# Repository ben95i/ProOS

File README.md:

# ProOS

ProOS is a self-hosted home automation and home server platform by Ben Provenzano III. It holds the configuration, firmware and code for every machine on the home network, from a Proxmox server down to a Pico W lamp controller, and one web app, **Automate**, controls all of it from a phone or browser.

The system has three layers. At the centre is one Proxmox server, which routes the network and runs storage, media, backups and the Automate web app in containers and VMs. Around the apartment, Raspberry Pis each take one role, such as a LED display, an audio receiver, a camera or a serial bridge. Below them, Pico W and Arduino microcontrollers switch the lamps, amps, outlets and bed. A button press in Automate goes to its API on the server, which calls the Pi or microcontroller that owns the device, so the browser never talks to the hardware directly. Every machine is defined entirely by its folder in this repo and is rebuilt over the network from a stock OS install, so any host can be replaced from scratch.

### Features

- **Automate web app.** One page that drives the apartment room by room: lamps and dimmers, ceiling lights, TVs, PCs (wake-on-LAN, sleep, power relays), the stereo amps' power, inputs, volume and subwoofers, the motorised bed and its LED strip, and the bathroom's motion-sensing light. Also live room status, scenes (room, lights, all on / off), temperature and humidity, weather, network host status, bookmarks, encrypted shared lists, photo and video upload, and a live doorway camera.
- **LED pixels.** Pis drive LED walls, grids and strips through Fadecandy or WS2812 directly, with C++ effects (text scroll, spectrum, maze, noise, orbits and more), video playback on the pixels, shuffle, and per-host brightness, kept in sync from one control.
- **Raspberry Pi modules.** A shared Pi base plus one small module per Pi: AirPlay and Bluetooth audio receivers, LED hosts, IR and motion-recording cameras with cloud upload, and the bedroom hub's serial bridge. Each Pi runs a read-only root filesystem so it survives losing power, recovers its own Wi-Fi, falls back to a setup hotspot, and compiles its C/C++ programs on install.
- **Microcontroller firmware.** Pico W lamp and light controllers and an HVAC thermostat (SmartThermo) with their own HTTP API, and Arduino/AVR boards for the bedroom hub, bed motor, switched outlets, the integrated amp and an IR remote hub.
- **Home server.** A Proxmox host running the services as containers and VMs: the router, SMB file shares (including one for vintage clients), an AFP server for classic Macs, Jellyfin with automatic MP3 mirroring, a UniFi controller, and a sandboxed desktop with a VPN kill switch. ZFS mirrored storage with automatic snapshots, rsync backups to encrypted external pools, encrypted on-demand storage regions, UPS monitoring, and backups of every VM and container, all triggered from the website.
- **One-command deployment.** `login.sh` deploys any host from this repo over SSH, with one passphrase prompt per terminal session for all keys.

The Automate website (`shared/html`, `shared/nodeapi`) has its own full reference, [`shared/CLAUDE.md`](shared/CLAUDE.md), imported at the end of this file.

## The system at a glance

One Proxmox server (`pve`) runs the network's services as LXC containers and KVM VMs. Raspberry Pis around the apartment each run one "module" (LEDs, cameras, audio), and small microcontrollers (Pico W, Arduino) drive lamps, amps and the bed. The Automate website, served from the `automate` container, is the remote control for all of it.

```
                    browser / phone
                          │  https://automate.home
                          ▼
  ┌─────────────────────────── pve (Proxmox, 192.168.1.8) ──────────────────────────┐
  │  automate LXC 106 ── lighttpd → node API ──┬─ HTTP → Pis (port 80 /api)          │
  │      /var/www/html/ram  ═══ bind ═══╗      ├─ HTTP → Pico W lamps (port 4000)    │
  │                                     ║      └─ LED hosts (ledhosts.txt)           │
  │  host tmpfs /mnt/ramdisk ◄══════════╝                                            │
  │      ▲ file-monitor.sh → apicmds.sh (backups, regions, start/stop VMs)           │
  │  files LXC 101 (SMB) · mgmt LXC 102 · legacy LXC 104 · media LXC 108             │
  │  router VM 100 · appletalk VM 103 · xana VM 105 · unifi VM 107                   │
  │  ZFS: rpool (boot) · tank/datastore (data, mirrored) · scratch SSD · ext. backups │
  └──────────────────────────────────────────────────────────────────────────────────┘
       Pis: brpi · ledwall · ledgrid · ledstrip · doorway · homepi · btpi · lrpi
       Microcontrollers: BathroomLight, LivingRoomLamp, SmartThermo (Pico W) · Bedroom hub, amp, IR hub (AVR)
```

## Folder map

Every top-level folder is one of four kinds. `login.sh` tells them apart by the marker file in the folder: `lxc.conf`, `qemu.conf` or `pc.conf` means a server ("nonpi"), anything else is a Pi module.

| Kind | Folders | Layout | Deployed by |
| --- | --- | --- | --- |
| Pi base | `rpi/` | Programs, `config/` (installer, systemd units, system configs), `effects/` (LED programs) | Copied to every Pi first, to `/opt/rpi` |
| Pi module | `brpi` `btpi` `doorway` `homepi` `ledgrid` `ledstrip` `ledwall` `lrpi` | `boot.sh`, `config/` (`installer.sh`, `brand.txt`, `config.txt`, other configs), extra programs or firmware | Overlaid onto `/opt/rpi` after the base, with `config/` sent to `/opt/rpi/config/module/` |
| Server (LXC / VM / PC) | `automate` `files` `legacy` `media` `mgmt` (LXC); `appletalk` `xana` (VM); `pve` (the Proxmox host); `brpc` (a physical PC) | `config/installer.sh` plus the files it installs; `lxc.conf` / `qemu.conf` / `pc.conf` marker | Tarred to `/tmp/config` and `installer.sh` run |
| Not deployed | `shared/` (Automate site, deployed with `automate` and every Pi), `wkst/` (this workstation, `install.sh` run by hand) | | |

`login.sh` refuses `rpi`, `wkst`, `shared`, `sources`, `login`, `logon` and `.ssh` as host names.

## Network and hosts

DNS domain `home`, LAN 192.168.1.0/24, gateway and DNS the router at 192.168.1.1. Addresses known from the code:

| Host | Kind | Address | What it is |
| --- | --- | --- | --- |
| `router` | VM 100 | 192.168.1.1 | The router, with two NICs passed through over PCIe (`hostpci0/1`); login is `admin@router`, not root. Configs in `pve/network/` (pfSense, EdgeRouter, UniFi backups) |
| `files` | LXC 101 | .4 | Samba file server (SMB2+): shares Data, Media, Scratch, Cameras, Games, MP3s, Regions, External |
| `mgmt` | LXC 102 | .7 | Management box: holds the SSH keys (`mgmt/keys/`, git-ignored) and runs `login.sh`; mounts the Projects share read-only at `/mnt/Projects` |
| `pve` | Proxmox host | .8 | Hypervisor; 4 NICs bonded 802.3ad into `vmbr0` |
| `appletalk` | VM 103 | | Netatalk 4 AFP server (built from `netatalk-4.4.3.tar.xz`) for vintage Macs |
| `legacy` | LXC 104 | .19 | Samba with `LANMAN1` minimum protocol, for old clients; started on demand from the website |
| `xana` | VM 105 | | Debian desktop over TigerVNC: Firefox in Firejail, Transmission behind a PIA WireGuard tunnel with kill switch and watchdog, retro themes |
| `automate` | LXC 106 | .16 | The Automate website and node API |
| `unifi` | VM 107 | | UniFi network controller |
| `media` | LXC 108 | .11 | Jellyfin, plus `mp3sync` (C++, `mp3sync.cpp`): watches the music library with inotify and mirrors it as MP3s into the MP3s share |
| `brpc` | PC | .17 | Bedroom Lenovo ThinkCentre: its own lighttpd + node API (`server-min.js`) and `webapi.sh` so Automate can sleep it; woken by wake-on-LAN |
| `brpi` | Pi | .15 | Bedroom Pi (wired, Wi-Fi off): AirPlay, serial bridge to the bedroom hub and the amp, relax sounds |
| `ledwall` | Pi | .12 (`lrxmit` in the API) | LEDwall: the 93-pixel LED ring (Fadecandy) and the living room's command host. Its `custom.js` serves `extcom` (living room stereo codes over serial on `/dev/ttyAMA0`), the white LED, the front button and the desktop PC power relay (`pc_power`) |
| `ledgrid` | Pi Zero | | WS2812 grid driven directly (`opcserver`) |
| `ledstrip` | Pi | | 3×60 strips (Fadecandy) |
| `doorway` | Pi | | IMX462 IR camera: `rtspcam` (RTSP on :8554/cam), `minimotion` recorder, `ldrdetect` day/night, rclone to Google Drive, Cameras share |
| `homepi` | Pi | | Family-home camera hub: `motion` with two cameras, uploads via rclone |
| `btpi` · `lrpi` | Pi | | Audio receivers: AirPlay (shairport-sync) and Bluetooth (BlueALSA) into a stereo; `btpi` adds Bluetooth to a vintage stereo, `lrpi` (formerly `stereo`) is the living room's, branded "Living Room" |
| `desk` | PC | .14 | Living room desktop, pinged by `wkststate` |
| `lrmlamp1` · `bthrlight1` | Pico W | .18 · .21 | Living room lamp, bathroom light (firmware in `automate/devices/`) |
| `lrthermo1` | Pico W | .3 | SmartThermo, the living room's HVAC thermostat (firmware in `automate/devices/SmartThermo/`) |
| `wkst` | Workstation | | This machine: mounts the `files` shares under `/mnt/*` with autofs (`auto.files`), detached while `files` is down by `share-watchdog.sh` (so this repo, `/mnt/Data/Projects/ProOS`, is the Data share) |

The Automate status menu (`shared/html/menus/statsmenu.txt`) and the LED host list (`menus/ledhosts.txt`) are the living lists of hosts the website talks to.

## Deployment: `login.sh`

`login.sh` runs on `mgmt`, where the repo is at `/mnt/Projects/ProOS` (its `ROOTDIR`), and needs `/opt/deploy` as a scratch folder. A host's key (`mgmt/keys/<host>.rsa` for servers, `rpi.rsa` for all Pis) has a passphrase when the host's folder holds an empty `ssh.pwd` marker file (`<host>/ssh.pwd`; for the Pi key, `rpi/ssh.pwd` or any Pi module's); all marked keys share one passphrase. Marked keys go through one `ssh-agent` per terminal session (keyed by the calling shell's PID, socket under `$XDG_RUNTIME_DIR/ssh-agents/`, or `/dev/shm/proos-<uid>/` without it): the first marked login in a terminal adds every marked key in one `ssh-add` call, so a single `Enter passphrase:` prompt unlocks them all (the script is its own `SSH_ASKPASS` prompter, run through bash by a two-line `askpass` wrapper it writes into the session folder, so no key path is shown; Enter skips a key for the rest of the session), and later runs reuse the agent. Unmarked keys are used straight from the file. Each connection uses `-o IdentitiesOnly=yes -i` with the host's key (its public key taken from the agent when unlocked), so ssh never offers the other loaded keys. The agent is removed by `login clearkeys`, by the `EXIT` trap in `mgmt/config/profile_ben`, when its shell is gone, or after 8 h; the passphrase itself is never stored. It checks port 22 with `nc`, then:

| Command | Does |
| --- | --- |
| `login <host>` | SSH shell as root (`admin` for `router`) |
| `login <host> sync` | Deploy: server → `DEPLOY_SERVER`, Pi → `DEPLOY_PI` |
| `login <pi> reset` | Deploy a Pi after deleting `/etc/rpi-conf.done`, so the installer's first-run phase runs again |
| `login <module> init <host>` | Deploy module `<module>` onto the Pi currently reachable as `<host>` (renames it to `<module>`) |
| `login <host> update` | Updates the host's packages: `apt-get update; apt-get upgrade` on a server, `rpi update` on a Pi. Given a host list (`login pve,files,automate update`), every host updates at once in its own tile |
| `login <host> reboot` | Reboots a server or a Pi after a 3 s Ctrl+C countdown (a Pi keeps its read-only or read-write mode); `login files,legacy reboot` reboots each in its own tile |
| `login <pi> <cmd>` | Runs `rpi <cmd>` on the Pi (see `rpi/rpi.sh`) |
| `login <host1>,<host2>,… [<cmd>]` | Opens one tmux tile per host (a new window when already inside tmux), each running `login <host> [<cmd>]` with the same `<cmd>` (not `init`). The keys are unlocked once before the tiles open and the tiles share that terminal's agent (`PROOS_AGENT_DIR`); each tile waits for a key before it closes. `mgmt` installs `/etc/tmux.conf` with `mouse on`, so a click selects a tile |
| `login clearkeys` | Forget this terminal's unlocked keys (stops its agent) |
| `login cmds` · `login rmtmp` | Command cheat sheet · delete deploy temp files and stop every session agent |

**A new Pi.** Start from stock Raspberry Pi OS with root SSH login and password authentication enabled, then run `login <module> init <host>`: the first connection falls back to the root password, and the installer replaces root's `authorized_keys` with `rpi/config/authorized_keys` (the public half of `mgmt/keys/rpi.rsa`, git-ignored) and installs an `sshd_config` that allows root by key only (`PermitRootLogin without-password`, `PasswordAuthentication no`).

After a deploy a menu offers re-deploy, update packages, reboot (a Pi reboots into read-only mode with `rpi ro`) or a shell.

**Server deploy.** Copies `<host>/config` to a temp folder (for `automate`, also `shared/html` and `shared/nodeapi` into it), tars it, `scp`s it to `/tmp`, untars to `/tmp/config` and runs `/tmp/config/installer.sh` as root. Every server installer follows the same shape: apt packages, users (`tank` uid 1000 and group `shared` gid 1000, which the LXC idmaps pass through unshifted), sshd config and `authorized_keys`, `profile`, `sysctl.conf`, `rc.local` + `rc-local.service` as the boot hook, service files, then deletes `/tmp/config`.

**Site icons.** The Automate site's Font Awesome sheet and fonts (`styles/icons.min.css`, `fonts/fa-*.woff2`) are not in the repo; they live only in the cache `/tmp/proos-fontcache` on `mgmt` (the repo is read-only there). Before every deploy of the site (`automate` and every Pi), `login.sh` checks the cache against the site with `shared/fontawesome/build-icons.py --check`, builds into it with `build-icons.py --out` when a page names an icon it lacks (or after a reboot cleared `/tmp`), and copies the cached files into the deploy's copy of the site (a work folder under `/opt/deploy` for a Pi), each step printed as an `Icons:` line. The cache stays after a deploy, so later deploys reuse it, and a lock file in it makes parallel deploys (tmux tiles) take turns. A failed build sends the cache's older build with a warning (icons added since show blank); with no build at all, or a cache that cannot be written, the site goes with every icon blank, also with a warning. The build needs `python3-fonttools` and `python3-brotli`, which `mgmt/config/installer.sh` installs.

**Pi deploy.** If the root filesystem is an overlay it first runs `rpi rw` and waits for the reboot. Then it rsyncs, in order: `rpi/` → `/opt/rpi`, a copy of `shared/html/` with the icons from the cache → `/opt/rpi/config/html/`, `shared/nodeapi/` → `/opt/nodeapi/`, `<module>/` → `/opt/rpi/` (excluding `config`, `photos` and `sources`), and `<module>/config/` → `/opt/rpi/config/module/` (replacing what an earlier deploy left there), writes the module name to `/opt/rpi/config/hostname` and runs `/opt/rpi/config/installer.sh`.

Because the module is copied over the base, **a module's files replace the base's files of the same name**: `<module>/boot.sh` replaces `rpi/boot.sh`. The one exception is the module's `config/`, which lands beside the base's as `/opt/rpi/config/module/`, so its `installer.sh` and `config.txt` do not replace the base's.

## Raspberry Pi platform (`rpi/`)

Requires Raspberry Pi OS on Debian **trixie**; the installer refuses anything else.

### Installer (`rpi/config/installer.sh`)

1. **First run only** (no `/etc/rpi-conf.done`): locale, time zone, `pi` user, a long apt package list (build tools, GStreamer, ffmpeg, Bluetooth, node, lighttpd, motion; no X11 desktop), purges cron, logrotate, swap, PulseAudio/PipeWire, cups and others, deletes old `rpi-*` units.
2. **Every run**: read-only boot partition, `config.txt`, sshd and key, `sysctl`, NetworkManager, journald (to RAM), systemd units from `config/systemd/` into `/etc/systemd/system/`, `/etc/netmode.sh` and `/etc/preinit.sh`.
3. **Node API**: moves `rpi/controller.js`, `rpi/ledparser.js` and `rpi/custom.js` over the shared ones in `/opt/nodeapi` (`npm install` only when `package.json` changed, tracked in `.deps.hash`).
4. **Website**: rsyncs the staged html into `/var/www/html` (keeping `ram/`), replaces the title `>Automate<` with the module's `brand.txt` name (this is how `main.js` picks the Pi or LED Pi page model), minifies, and gives `www-data` sudo on `servercmds.sh` and `relaxrun.sh` only.
5. Bluetooth, ALSA, Samba USB share, udev USB automount, motion defaults, hostname and `/etc/hosts`.
6. **`config/cleanup.sh`**, once per Pi (skipped while `/etc/rpi-cleanup.done` exists; delete it and deploy to run it again), so the system fits an 8 GB card: swaps `libopencv-dev` for `libopencv-core-dev` + `libopencv-videoio-dev`; purges the X11 desktop, the `arduino` apt package and its AVR toolchain, USB Wi-Fi dongle firmware, the `v6` kernels, every kernel but the running and newest, and all kernel headers; deletes `arduino-cli` and `~/.arduino15` unless the module's `config/installer.sh` installs it (only `brpi` does); installs `config/dpkg-nodoc.conf` as `/etc/dpkg/dpkg.cfg.d/01-nodoc` and deletes docs, man pages and non-English translations; clears the apt lists and npm cache.
7. **`config/compile.sh`**: builds the C/C++ programs (below).
8. First run: enables `ssh avahi-daemon proinit NetworkManager timesyncd`, disables the rest (lighttpd, bluetooth, smbd, hostapd …), touches `/etc/rpi-conf.done`.
9. Runs `/opt/rpi/config/module/installer.sh` (the module's own installer, from `<module>/config/installer.sh`), then **deletes `/opt/rpi/config/module`**; restarts lighttpd and nodeapi; links `/usr/bin/rpi` → `rpi.sh`; deletes `/opt/rpi/config`.

### Boot sequence

`proinit.service` (after `network-online.target`) runs `/etc/netmode.sh boot`, then `/opt/rpi/boot.sh` — the module's own boot script. Module boot scripts start only the services that module needs, passing settings through `systemctl set-environment` (e.g. `rpi_ledtype`, `rpi_ledmaxbright`, `rpi_gpipin_1`, `rpi_imx*`), which the `rpi-*.service` units read. Nothing module-specific is enabled at boot; services are started by `boot.sh`.

### Read-only root

Pis run with an OverlayFS root, so writes go to RAM and the Pi can be unplugged safely (the SD cards used to corrupt when a Pi lost power). `rpi rw` / `rpi ro` reboot into read-write / read-only (via `raspi-config nonint disable_overlayfs`/`enable_overlayfs`); the boot partition is remounted rw only for the moment it is written. Anything that must survive a reboot on a Pi has to be written in rw mode or to the boot partition / a USB drive.

### Networking (`rpi/config/netmode.sh`)

`boot`, `client`, `apd`, `delwifi`, `watchdog`. Wi-Fi credentials live on the boot partition (`/boot/firmware/wpa.conf`, `NAME|$|PASSWORD`, written by the website's Wi-Fi setup through `servercmds.sh confwpa`). Flags on the boot partition: `disable.wifi`, `apd.enable` (start as hotspot `RPiHotspot`). With no known network at boot the Pi falls back to hotspot mode with a captive DNS (`captive.conf`). `rpi-netwatchdog.service` (`netmode.sh watchdog`) recovers a hung Wi-Fi chip in stages without writing to disk; tunables are at the top of the script.

### `rpi` command (`rpi/rpi.sh`)

`ro`, `rw`, `update`, `expand`, `net`, `wifiscan`, `wifistats`, `togglenet`, `client`, `apd`, `apdonboot`, `enablewifi`/`disablewifi`, `delwifi`, `resetbt`, `restart-alsa`, `temp`, `jl`/`jh` (journal), `running`/`active`/`timers`/`loadtimes`. The website's Pi options call these through `servercmds.sh`, which logs to `/var/www/html/ram/sysout.txt`.

### Pi-side node API

The Pis run the same `shared/nodeapi/server.js`, but `rpi/controller.js` replaces the server's command dispatch: `server <cmd>` → `sudo servercmds.sh <cmd>`, `confwpa` → Wi-Fi setup, everything else → `exeCustom()` in `custom.js`. The base `rpi/custom.js` is a stub; a module with real commands ships `config/custom.js`, which its `config/installer.sh` copies over it:

- `brpi/config/custom.js`: serial via `ztermcom` (one FIFO queue, at most 8 waiting) to the amp on `/dev/ttyUSB0` and the bedroom hub on `/dev/ttyAMA0` (`hwcom`, `usbcom`), amp power/inputs/volume, `bed_leds_hex_set`, relax sounds (`relaxmenu.txt`, `relaxrun.sh` → `rpi-relaxloop.service`), activity LED flash.
- `ledwall/config/custom.js`: `extcom` (serial), `front_btn` (LED shuffle), white LED, `pc_power`.

`rpi/ledparser.js` replaces the server's LED fan-out with the local effect runner: it spawns one effect binary from `/opt/rpi/effects`, plays videos through `mp4toleds`, and sets brightness through the proxy. Shuffle picks from `menus/ledshuffle.txt`. Each command also records what the pixels show, which `fc_status` (`/api?action=leds&arg=fc_status`) answers as JSON with the brightness: `{ effect, state, color, brightness }`, state `off` (stopped, or black), `active`, `paused` (also an effect that ended on its own) or `color` (RRGGBB); the server's Pixels window reads it.

### Local services and ports

| Program (source) | Unit | Port / interface | Role |
| --- | --- | --- | --- |
| `gposerver` (`gposerver.cpp`) | `rpi-gposerver` | HTTP 127.0.0.1:8770 `/gpio?pin=&state=HIGH\|LOW\|TOGGLE` | GPIO outputs for the node API |
| `pinmon` | `rpi-pinmon-1` | GPIO input | On a falling edge runs `/opt/rpi/<cmd>.sh` (ledwall: `front_btn.sh`, which calls the local API) |
| `ldrdetect` | `rpi-ldrdetect` | GPIO | Light sensor day/night for the camera |
| `opcserver` (`effects/`) | `rpi-opcserver` | OPC :7890, HTTP :7892 | Drives WS2812 directly (ws281x DMA library); args `<WxHgrid> <power limit> <rotation>` |
| `fcserver` (prebuilt) + `fcproxy` | `rpi-fcserver`, `rpi-fcproxy` | effects → :7890 proxy → :7891 fcserver; HTTP :7892 brightness | Fadecandy hosts; layouts in `effects/fc.<ledtype>.json` |
| `mp4toleds` | `rpi-mp4toleds` | OPC client, HTTP :7860 `/api?video=` | Plays `effects/videos/*.mp4` on the pixels |
| Effects: `textscroll maze oscope spectro noise orbits miami stripes chase writecolor` | spawned by `ledparser.js` | OPC client → :7890 | One running at a time; share `ledlayout.cpp` and `opcclient.cpp` |
| `rtspcam` | `rpi-rtspcam` | RTSP :8554/cam | IMX462 hardware H.264 (doorway; notes in `rtspcam.md`) |
| `minimotion` | `rpi-minimotion` | | Motion recorder: reads the RTSP stream, records in `/mnt/ramdisk`, copies clips out (`doorway/minimotion.conf`) |
| `ztermcom` (`ztermcom.c`) | CLI | serial | Framed serial request/response to Arduino hubs |
| node API · lighttpd | `nodeapi`, `lighttpd` | :3000 · :80 | Same as the Automate server |

`ledtype.txt` (written by a LED module's `config/installer.sh`) names the layout: `93ringinv` (ledwall), `3x60strips` (ledstrip), `16x16grid` (ledgrid).

### Compiling (`rpi/config/compile.sh`)

C/C++ sources are compiled on the Pi at install time. `build()` compiles only when the source's sha256 differs from its archived copy in `/opt/source-backup`, the binary is missing, or a shared dependency changed (`opcutils.*` / `httpapiserver.*` for the servers, `ledlayout.*` / `opcclient.*` for the effects); the source is then **moved** into `/opt/source-backup`. A new program needs a `build`/`effect`/`tool` line here. The ws281x library is built once into `/usr/local`.

## Microcontroller firmware

| Folder | Board | Talks to | Role |
| --- | --- | --- | --- |
| `automate/devices/BathroomLight/` | Pico W | HTTP :4000 | Bathroom light + C4002 mmWave sensor; API reference `.md` alongside |
| `automate/devices/LivingRoomLamp/` | Pico W | HTTP :4000 | Living room lamp (switched lamp + dimmable LED, rotary encoder); derived from BathroomLight |
| `automate/devices/SmartThermo/` | Pico W | HTTP :4000 | HVAC thermostat (furnace + central AC): W1 / Y1 / G relays, DHT22, ST7735R TFT display, every interlock and lockout from the HVAC control reference, watchdog; API reference `.md` alongside; derived from BathroomLight |
| `automate/devices/InfraredRemoteHub/` | Arduino | serial | Sends IR codes to the stereo's preamp, DAC and sub amp |
| `brpi/BedroomHub/` | AVR | brpi `/dev/ttyAMA0` | Bedroom hub #1: relays, temperature/humidity (DHT), two external serial ports |
| `brpi/BedroomHubExt/` | ATmega328P | hub serial #2 | WS2812 bed strip, switched outlets, bed motor (EAGLE board files alongside) |
| `brpi/BedroomPowerExt/` | AVR | serial | 2×120 VAC + 12 VDC switched controller |
| `brpi/IntegratedAmp/` | Arduino Uno | brpi `/dev/ttyUSB0` | Integrated amp controller; flashed from the Pi with `brpi/update-amp.sh` (`update-bedhub.sh` for the hub) via `arduino-cli` |

Pico firmware is built with the arduino-pico core (`build/rp2040.rp2040.rpipicow/`, git-ignored); Wi-Fi credentials are in `creds.h` (git-ignored). Pico commands use the `http://<host>:4000/api?<cmd>,,<value>~` form, errors as text under HTTP 200.

## Proxmox host (`pve/`)

`pve/config/installer.sh` sets up the host: no-subscription apt source, NIC name pinning (`50-pve-nic*.link`) and the bonded `interfaces`, IOMMU / PCIe passthrough (`grub`, `blacklist.conf`), swap moved to the scratch SSD, `fstab`, postfix mail relay (`sasl_passwd`, git-ignored), apcupsd (APC SC620 UPS), smartd, lm-sensors, ZFS auto-snapshots on `tank/datastore` (hourly/daily/weekly/monthly cron, no 15-minute), scrub/trim cron, `sys-check` and `kernelclean` tools, and the services below. `pve/qemu.conf` is only a placeholder so `login.sh` treats `pve` as a server. `pve/README.txt` holds the ZFS runbooks (new mirror, encrypted backup drive, replacing a data or boot drive) and `pve/zfsman` is a ZFS helper.

Storage: `rpool` (boot, ZFS), `tank` mirrored with `tank/datastore` at `/mnt/datastore` (`data`, `media`, `.regions`), a scratch SSD at `/mnt/pve/scratch` (camera footage, downloads, MP3s, uploads, swap), encrypted external backup pools listed in `bkpdrives.txt` attached under `/mnt/extbkps`.

### Website → host commands

This is how the Automate Server window controls the host:

1. The host mounts a 128 MB tmpfs at `/mnt/ramdisk` (owner `tank:shared`, setgid), bind-mounted into the automate LXC as `/var/www/html/ram`.
2. The node API's `server <name>` command appends to `ram/sysout.txt` and creates an empty `ram/<name>.txt`.
3. `file-monitor.service` (`pve/config/file-monitor.sh`) watches the ramdisk with inotify, claims each `*.txt` trigger atomically into `spool/`, and runs `/usr/bin/apicmds.sh <name> /mnt/ramdisk` in the background (at most 4 at once), appending output to `sysout.txt`. Data files are on its `IGNORE` list (`sysout.txt`, `*.save.txt`, `*.lock`, `pwd.txt`, `fusearch.txt`, `drives.txt`, `*.tmp`) — a new data file kept in `ram/` must be added there or it will be consumed as a command.
4. The website polls `sysout.txt` into the log window.

`apicmds.sh` commands: `backupstd`, `backupchk` (rsync to external pools, lock `backupsvr.lock`), `last_backup_dates`, `attach_bkps`, `detach_bkps`, region mounts (`mnt_/unmnt_arch_region` gocryptfs Archive, `mnt_/unmnt_ram_region`, `mnt_/unmnt_snap_region`, `unmnt_all`), `pve_listsnaps`, `start/stop` for `legacy` (LXC 104), `xana` (105, plus `restorexana`), `unifi` (107), `atalk` (103), `rebootrouter`, `syslog` (`sys-check`), `pve_vmsbkp`, `clearlog`. A new server command needs a case here and an option in `shared/html/server.js`.

### Persistent state and backups

- **Website state** (`bookmarks.save.txt`, `lists.save.txt`, their lock and password files) lives only in the RAM disk. `hourly.sh` (`hourlyjob.timer`, and `hourlyjob-sd.service` on shutdown) copies them to `/mnt/datastore/data/Documents/` (`Bookmarks.txt`, `Lists.txt`, keeping a `.bak`), and restores them into the RAM disk when they are missing after a reboot.
- **`pve_vmsbkp`** vzdumps every guest, copies the archives into `pve/vmbkps/`, and **overwrites `<host>/lxc.conf`, `appletalk/qemu.conf`, `xana/qemu.conf` and `pve/vmbkps/vzdump-qemu-*.conf` in this repo** from `/etc/pve`. Those files are generated snapshots of the live config: edit the guest in Proxmox, not here.

## Conventions across the repo

Code style rules (naming, comments, shell, JavaScript and CSS) live only in [`CODESTYLE.md`](CODESTYLE.md), imported at the end of this file. This section covers how the repo is organised and worked on.

- A new Pi service is a `rpi-<name>.service` in `rpi/config/systemd/`, not enabled, started from the module's `boot.sh` with settings passed by `systemctl set-environment`.
- A new Pi module is a folder with `boot.sh` and `config/{installer.sh,brand.txt,config.txt}`, the same `config/installer.sh` layout as a server (its installer runs after the base's, from `/opt/rpi/config/module/`); `brand.txt` becomes the page title, AirPlay/Bluetooth/Samba name.
- A new server is a folder with `config/installer.sh` and a marker file; add its key as `mgmt/keys/<name>.rsa`, plus an empty `<name>/ssh.pwd` if the key has the shared passphrase.
- Secrets are git-ignored and must stay out of commits and docs: `mgmt/keys/`, `*.rsa`, `*.pub`, `*.pem`, `*.crt`, `*.key`, `authorized_keys`, `auto.creds`, `creds.h`, `sasl_passwd`, `pia-wg.conf`. Don't print their contents.
- `._*` and `.DS_Store` files are macOS metadata, ignored by git; leave them alone.
- Large binaries in the tree (`pve/vmbkps/*.zst`, `rpi/effects/videos/`, `shared/fontawesome/`, firmware builds, photos) are backups or assets, not sources to read. Photos of the builds are in `btpi/photos`, `ledstrip/photos`, `ledwall/photos` and `pve/photos`, and are not deployed.
- A repo script is run through `bash` (`bash login.sh`, `bash www-minify.sh`), not by its execute bit, which mgmt sees as stored on the server: a file rewritten over the SMB share comes back `0644`, and this workstation's mount shows every file as `0755` whatever it is. A script a program must execute itself (ssh-add's `SSH_ASKPASS`) gets a wrapper written outside the repo; the Pi and server deploys `chmod +x` their installers.
- There is no git or node in this workstation's shell, and no test suite: verify shell changes by reading them, and the website as described in the Automate reference.

Code style: [CODESTYLE.md](CODESTYLE.md)

@CODESTYLE.md

## Automate website reference

Automate reference: [shared/CLAUDE.md](shared/CLAUDE.md)

@shared/CLAUDE.md

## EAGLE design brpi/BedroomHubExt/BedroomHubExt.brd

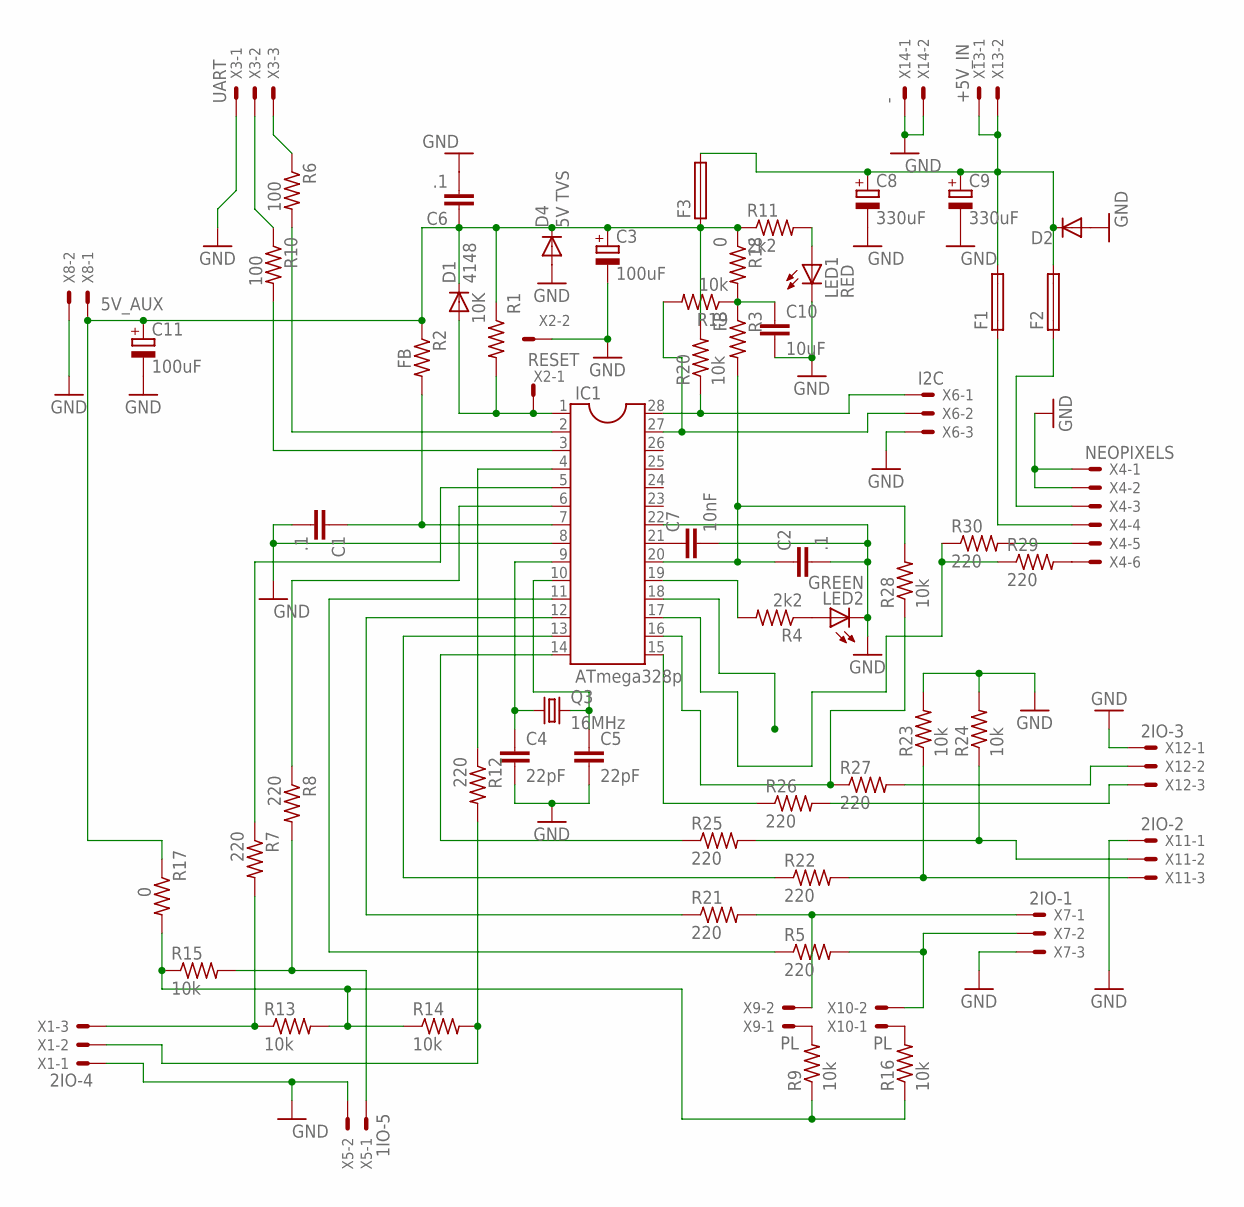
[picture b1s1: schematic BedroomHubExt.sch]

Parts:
C1, C2, C6: .1; C1210K
C3, C11: 100uF; E2,5-7
C4, C5: 22pF; C1210K
C7: 10nF; C050-024X044
C8, C9: 330uF; E5-10,5
C10: 10uF; C1210K
D1: 4148; DO35-7
D2: 1N5624; DO201-15
D4: 5V TVS; DO07
F1, F2, F3: 19560
IC1: ATmega328p; DIL28-3
LED1: RED; LED3MM
LED2: GREEN; LED3MM
Q3: 16MHz; HC49/S
R1: 10K; 0309/10
R2, R3: FB; 0309/10
R4, R11: 2k2; 0309/10
R5, R21, R22, R25: 220; 0207/7
R6, R10: 100; 0309/10
R7, R8, R12, R26, R27, R29, R30: 220; 0309/10
R9, R13, R14, R15, R16, R19, R20, R23, R24: 10k; R1210
R17, R18: 0; 0309/10
R28: 10k; 0309/10
X1: 2IO-4; 22-23-2031
X2: RESET; 22-23-2021
X3: UART; 22-23-2031
X4: NEOPIXELS; 22-23-2061
X5: 1IO-5; 22-23-2021
X6: I2C; 22-23-2031
X7: 2IO-1; 22-23-2031
X8: 5V_AUX; 22-23-2021
X9, X10: PL; 22-23-2021
X11: 2IO-2; 22-23-2031
X12: 2IO-3; 22-23-2031
X13: +5V_IN; 22-23-2021
X14: -; 22-23-2021

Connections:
GND: C1.2, C2.2, C3.-, C4.2, C5.2, C6.2, C7.2, C8.-, C9.-, C10.2, C11.-, D2.A, D4.A, IC1.8, IC1.22, LED1.K (C), LED2.K (C), R23.2, R24.2, X1.1, X2.2, X3.1, X4.1, X4.2, X5.2, X6.3, X7.3, X8.2, X11.1, X12.1, X14.1, X14.2
unnamed: IC1.2, R6.2
unnamed: D1.A, IC1.1, R1.2, X2.1
unnamed: IC1.3, R10.2
unnamed: C2.1, IC1.20, R3.2, R28.2
unnamed: R24.1, R25.2, X11.2
unnamed: R26.2, X12.3
unnamed: LED1.A, R11.2
unnamed: IC1.19, R4.2
unnamed: IC1.15, R26.1
unnamed: IC1.16, R27.1, R28.1
unnamed: IC1.17, R29.1, R30.1
unnamed: C4.1, IC1.9, Q3.1
unnamed: C5.1, IC1.10, Q3.2
unnamed: C7.1, IC1.21
unnamed: LED2.A, R4.1
unnamed: IC1.14, R25.1
unnamed: IC1.13, R22.1
unnamed: IC1.12, R21.1
unnamed: IC1.11, R5.1
unnamed: IC1.6, R8.1
unnamed: IC1.5, R7.1
unnamed: IC1.4, R12.1
unnamed: C3.+, C6.1, C11.+, D1.C, D4.C, F3.1, R1.1, R2.1, R11.1, R17.1, R18.1, R20.2, X8.1
unnamed: R10.1, X3.2
unnamed: R7.2, R13.1, X1.3
unnamed: R8.2, R15.2, X5.1
unnamed: R5.2, X7.2, X10.2
unnamed: R21.2, X7.1, X9.2
unnamed: R12.2, R14.2, X1.2
unnamed: C1.1, IC1.7, R2.2
unnamed: R6.1, X3.3
unnamed: IC1.28, R20.1, X6.1
unnamed: R9.1, R13.2, R14.1, R15.1, R16.1, R17.2
unnamed: IC1.27, R19.2, X6.2
unnamed: C10.1, R3.1, R18.2, R19.1
unnamed: R22.2, R23.1, X11.3
unnamed: R9.2, X9.1
unnamed: R16.2, X10.1
unnamed: R27.2, X12.2
unnamed: R29.2, X4.6
unnamed: R30.2, X4.5
unnamed: F1.1, X4.4
unnamed: F2.1, X4.3
unnamed: C8.+, C9.+, D2.C, F1.2, F2.2, F3.2, X13.1, X13.2

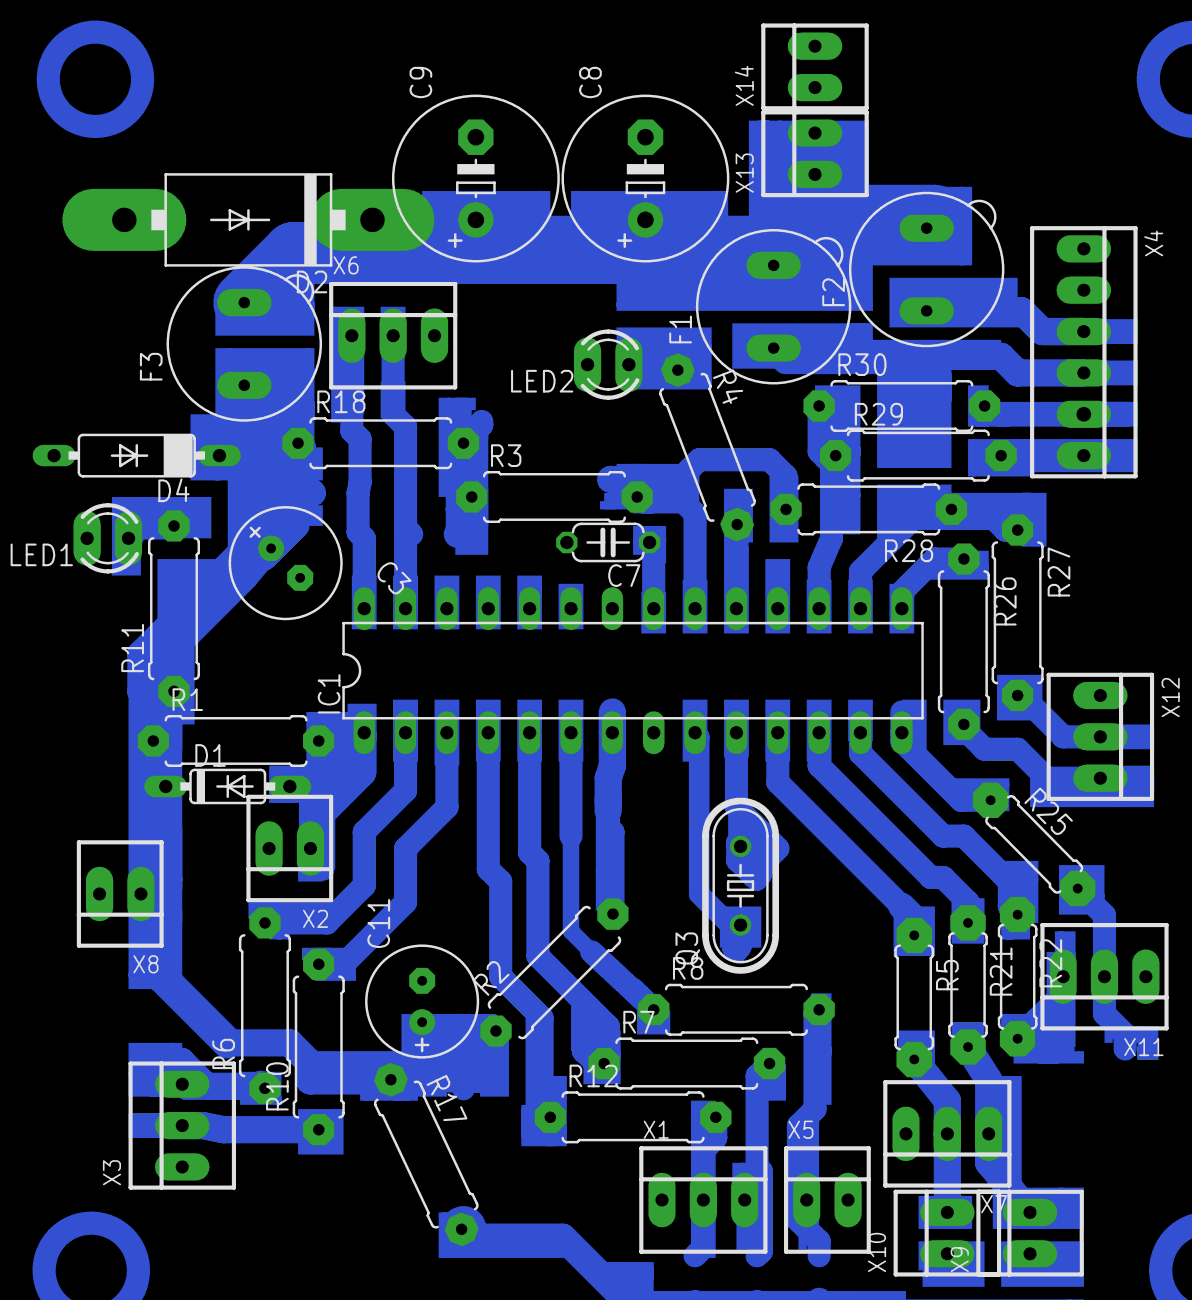
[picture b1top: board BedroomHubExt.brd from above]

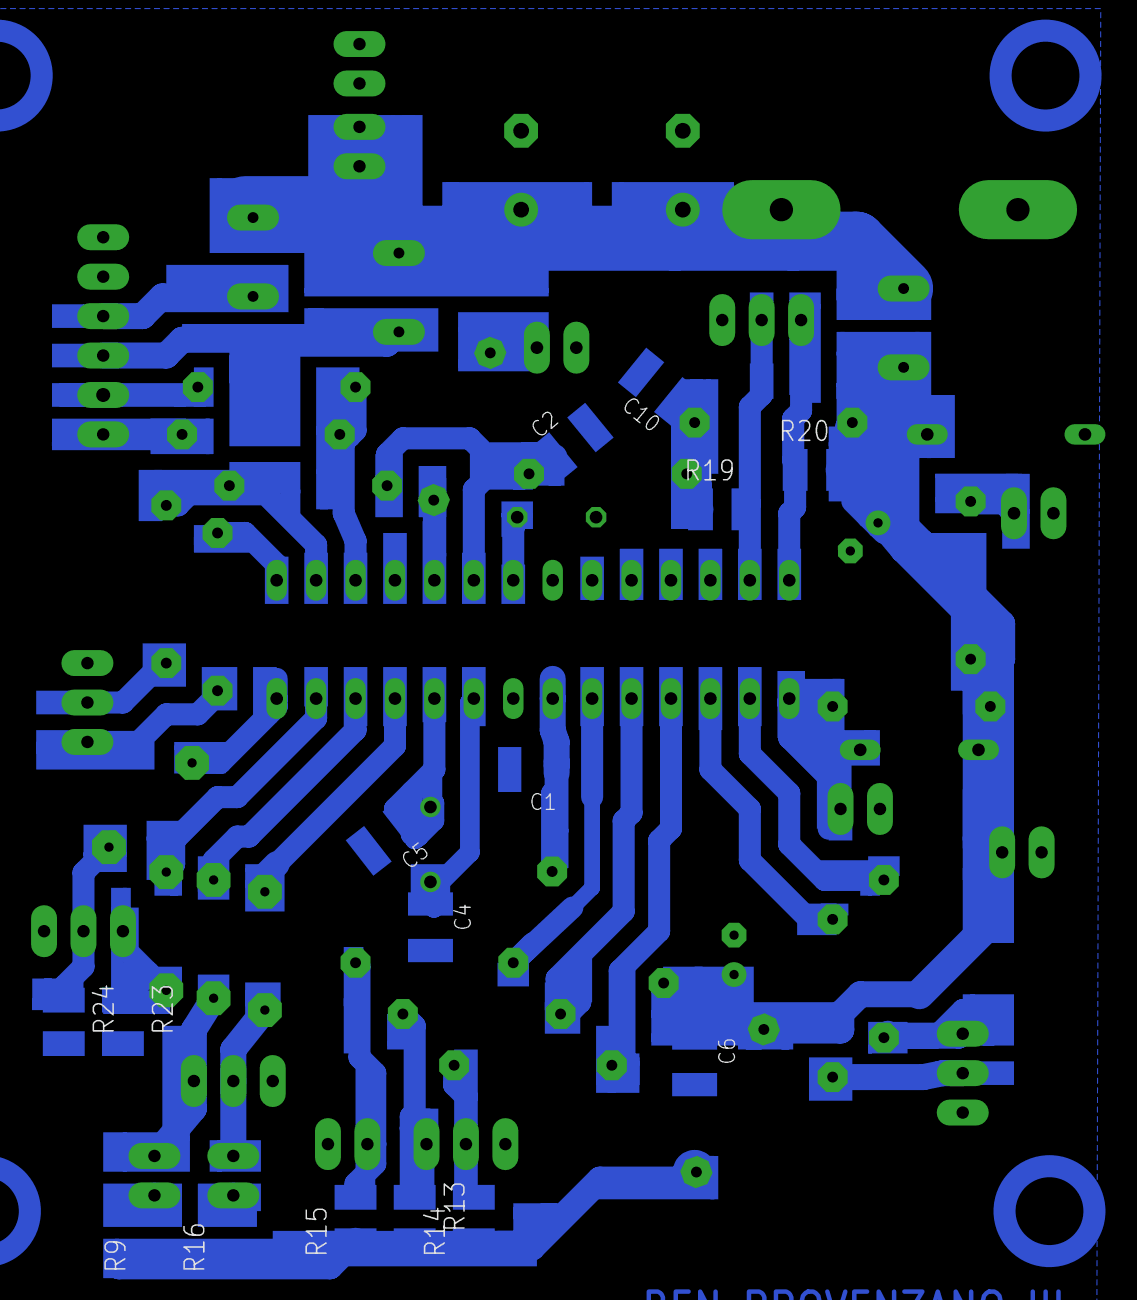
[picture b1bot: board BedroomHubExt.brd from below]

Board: 2 copper layers, 65 parts (15 on the bottom side), 45 nets.

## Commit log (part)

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2025-05-11 2025-05-11 18:35
2025-05-12 2025-05-12 18:59
2025-05-14 2025-05-13 21:40
2025-05-18 2025-05-18 18:22
2025-05-19 2025-05-18 20:48
2025-05-19 2025-05-19 09:37
2025-05-21 2025-05-20 20:56
2025-05-21 2025-05-20 21:26
2025-05-21 2025-05-20 21:30
2025-05-22 2025-05-22 19:53
2025-05-23 2025-05-22 20:05
2025-05-23 2025-05-22 21:07
2025-05-24 2025-05-24 14:00
2025-05-24 2025-05-24 18:21
2025-05-24 2025-05-24 18:24
2025-05-24 2025-05-24 18:32
2025-05-24 2025-05-24 18:39
2025-05-25 2025-05-24 20:45
2025-05-25 2025-05-24 20:58
2025-05-25 2025-05-24 21:00
2025-05-25 2025-05-24 21:14
2025-05-25 2025-05-24 22:14
2025-05-25 2025-05-24 22:55
2025-05-26 2025-05-26 18:52
2025-05-26 2025-05-26 19:23
2025-05-27 2025-05-26 20:52
2025-06-01 2025-05-31 23:49
2025-06-01 2025-05-31 23:57
2025-06-01 2025-06-01 00:26
2025-06-01 2025-06-01 10:28
2025-06-02 2025-06-02 07:59
2025-06-03 2025-06-02 20:59
2025-06-04 2025-06-03 21:10
2025-06-04 2025-06-03 21:45
2025-06-05 2025-06-05 13:07
2025-06-05 2025-06-05 13:40
2025-06-05 2025-06-05 14:03
2025-06-10 2025-06-10 15:41
2025-06-12 2025-06-12 19:07
2025-06-13 2025-06-12 20:02
2025-06-13 2025-06-13 19:57
2025-06-18 2025-06-17 21:25
2025-06-19 2025-06-19 09:08
2025-06-19 2025-06-19 13:37
2025-06-19 2025-06-19 14:00
2025-06-19 2025-06-19 15:09
2025-06-19 2025-06-19 19:30
2025-06-24 2025-06-23 22:11
2025-06-25 2025-06-25 11:12
2025-06-26 2025-06-25 21:07
2025-06-26 2025-06-26 06:44
2025-06-29 2025-06-29 16:43
2025-06-29 2025-06-29 19:04
2025-06-30 2025-06-29 20:31
2025-06-30 2025-06-29 21:14
2025-06-30 2025-06-29 21:20
2025-06-30 2025-06-30 13:09
2025-07-01 2025-06-30 21:16
2025-07-03 2025-07-02 21:12
2025-07-03 2025-07-02 21:22
2025-07-03 2025-07-03 06:38
2025-07-04 2025-07-03 21:28
2025-07-05 2025-07-05 17:04
2025-07-06 2025-07-05 23:03
2025-07-06 2025-07-06 10:53
2025-07-06 2025-07-06 12:31
2025-07-06 2025-07-06 15:21
2025-07-06 2025-07-06 19:50
2025-07-07 2025-07-06 20:30
2025-07-07 2025-07-06 21:43
2025-07-07 2025-07-06 22:06
2025-07-07 2025-07-06 22:15
2025-07-07 2025-07-06 22:19
2025-07-07 2025-07-06 22:24
2025-07-07 2025-07-07 08:06
2025-07-07 2025-07-07 10:30
2025-07-07 2025-07-07 13:40
2025-07-07 2025-07-07 13:48
2025-07-07 2025-07-07 13:58
2025-07-07 2025-07-07 18:42
2025-07-10 2025-07-09 20:02
2025-07-10 2025-07-09 20:03
2025-07-10 2025-07-09 21:40
2025-07-10 2025-07-10 19:08
2025-07-11 2025-07-10 22:21
2025-07-11 2025-07-11 08:22
2025-07-11 2025-07-11 13:32
2025-07-11 2025-07-11 15:32
2025-07-12 2025-07-12 12:05
2025-07-13 2025-07-13 14:49
2025-07-13 2025-07-13 17:35
2025-07-13 2025-07-13 18:09
2025-07-13 2025-07-13 18:20
2025-07-13 2025-07-13 18:24
2025-07-13 2025-07-13 18:51
2025-07-13 2025-07-13 18:55
2025-07-14 2025-07-13 21:42
2025-07-14 2025-07-14 12:27
2025-07-14 2025-07-14 13:48
2025-07-15 2025-07-14 20:56
2025-07-16 2025-07-16 15:58
2025-07-17 2025-07-16 21:13
2025-07-17 2025-07-16 21:20
2025-07-17 2025-07-16 21:52
2025-07-18 2025-07-18 07:56
2025-07-19 2025-07-19 09:46
2025-07-19 2025-07-19 18:41
2025-07-19 2025-07-19 19:46
2025-07-20 2025-07-20 08:31
2025-07-22 2025-07-21 21:49
2025-07-22 2025-07-21 21:53
2025-07-23 2025-07-22 20:32
2025-07-23 2025-07-22 20:35
2025-07-24 2025-07-24 06:55
2025-07-25 2025-07-25 12:32
2025-07-26 2025-07-25 22:35
2025-07-26 2025-07-26 10:30
2025-07-27 2025-07-27 08:31
2025-07-27 2025-07-27 10:23
2025-07-27 2025-07-27 10:41
2025-07-27 2025-07-27 11:21
2025-07-27 2025-07-27 12:32
2025-07-27 2025-07-27 18:54
2025-07-28 2025-07-27 20:13
2025-07-28 2025-07-27 22:05
2025-07-28 2025-07-28 06:17
2025-07-28 2025-07-28 09:01
2025-07-28 2025-07-28 09:30
2025-07-28 2025-07-28 09:45
2025-07-28 2025-07-28 18:41
2025-07-28 2025-07-28 18:42
2025-07-28 2025-07-28 19:39
2025-07-28 2025-07-28 19:41
2025-07-29 2025-07-28 20:06
2025-07-29 2025-07-28 20:23
2025-07-29 2025-07-29 19:21
2025-07-30 2025-07-29 20:54
2025-07-31 2025-07-31 05:57
2025-08-02 2025-08-01 20:30
2025-08-02 2025-08-01 21:41
2025-08-02 2025-08-01 21:50
2025-08-02 2025-08-01 22:01
2025-08-02 2025-08-02 15:50
2025-08-03 2025-08-02 20:02
2025-08-03 2025-08-02 20:22
2025-08-03 2025-08-02 20:27
2025-08-03 2025-08-03 10:32
2025-08-03 2025-08-03 17:13
2025-08-03 2025-08-03 17:18
2025-08-04 2025-08-03 20:47
2025-08-04 2025-08-04 08:16
2025-08-04 2025-08-04 16:17
2025-08-04 2025-08-04 17:15
2025-08-05 2025-08-05 19:44
2025-08-06 2025-08-06 10:35
2025-08-07 2025-08-06 20:23
2025-08-07 2025-08-06 21:05
2025-08-07 2025-08-07 06:35
2025-08-07 2025-08-07 16:59
2025-08-08 2025-08-08 13:26
2025-08-08 2025-08-08 14:00
2025-08-09 2025-08-09 19:02
2025-08-09 2025-08-09 19:27
2025-08-10 2025-08-09 21:05
2025-08-10 2025-08-09 21:49
2025-08-10 2025-08-10 15:15
2025-08-10 2025-08-10 16:49
2025-08-10 2025-08-10 18:17
2025-08-11 2025-08-10 20:38
2025-08-11 2025-08-11 08:43
2025-08-11 2025-08-11 15:08
2025-08-11 2025-08-11 15:15
2025-08-11 2025-08-11 16:08
2025-08-11 2025-08-11 19:22
2025-08-11 2025-08-11 19:36
2025-08-12 2025-08-11 21:02
2025-08-13 2025-08-12 21:07
2025-08-13 2025-08-13 18:55
2025-08-16 2025-08-16 11:19
2025-08-16 2025-08-16 18:40
2025-08-17 2025-08-16 20:00
2025-08-17 2025-08-16 21:39
2025-08-17 2025-08-17 07:55
2025-08-17 2025-08-17 17:06
2025-08-17 2025-08-17 17:48
2025-08-17 2025-08-17 18:40
2025-08-17 2025-08-17 19:48
2025-08-18 2025-08-17 20:12
2025-08-18 2025-08-18 14:44
2025-08-21 2025-08-21 17:37
2025-08-22 2025-08-21 21:05
2025-08-24 2025-08-24 08:51
2025-08-25 2025-08-24 21:18
2025-08-31 2025-08-31 12:58
2025-09-04 2025-09-03 20:43
2025-09-04 2025-09-04 10:06
2025-09-06 2025-09-05 22:36
2025-09-08 2025-09-08 12:34
2025-09-08 2025-09-08 14:44
2025-09-08 2025-09-08 19:58
2025-09-13 2025-09-13 19:29
2025-09-13 2025-09-13 19:37
2025-09-14 2025-09-13 22:15
2025-09-14 2025-09-14 13:09
2025-09-14 2025-09-14 14:42
2025-09-14 2025-09-14 19:35
2025-09-15 2025-09-15 11:39
2025-09-15 2025-09-15 13:55
2025-09-15 2025-09-15 14:39
2025-09-15 2025-09-15 19:41
2025-09-19 2025-09-19 19:05
2025-09-20 2025-09-20 10:28
2025-09-21 2025-09-21 13:38
2025-09-22 2025-09-21 20:51
2025-09-22 2025-09-22 13:11
2025-09-23 2025-09-23 17:50
2025-09-24 2025-09-24 07:49
2025-09-24 2025-09-24 13:35
2025-09-24 2025-09-24 17:39
2025-09-25 2025-09-25 16:51
2025-09-27 2025-09-27 17:41
2025-09-28 2025-09-27 20:57
2025-09-29 2025-09-28 21:06
2025-10-03 2025-10-03 07:52
2025-10-03 2025-10-03 14:25
2025-10-04 2025-10-03 20:18
2025-10-04 2025-10-03 20:31
2025-10-04 2025-10-04 15:45
2025-10-04 2025-10-04 16:11
2025-10-09 2025-10-09 13:15
2025-10-10 2025-10-10 08:37
2025-10-10 2025-10-10 10:59
2025-10-10 2025-10-10 13:16
2025-10-10 2025-10-10 15:48
2025-10-13 2025-10-13 17:49
2025-10-13 2025-10-13 19:57
2025-10-15 2025-10-14 20:53
2025-10-15 2025-10-14 21:04
2025-10-16 2025-10-16 17:10
2025-10-19 2025-10-19 18:25
2025-10-23 2025-10-23 06:20
2025-10-23 2025-10-23 18:55
2025-10-26 2025-10-26 07:52
2025-10-26 2025-10-26 07:55
2025-10-26 2025-10-26 08:00
2025-10-27 2025-10-27 19:24
2025-10-29 2025-10-29 06:20
2025-10-31 2025-10-31 19:50
2026-04-12 Legacy release
2026-04-12 2025-11-25
2026-04-12 2026-03-01
2026-04-12 2026-03-01 #2
2026-04-12 2026-04-12
2026-04-12 add extra VMs
2026-04-13 2026 R2
2026-04-13 updated network
2026-04-16 added IP range to SMB configuration
2026-04-20 updated website labels and added new animated shooting stars background
2026-04-20 added wkst linux settings
2026-04-22 optimized animation rendering
2026-04-24 switch to fastfetch
2026-04-25 switched from python GPIO control to native C++
2026-04-26 added C++ LDR controller (replaces python)
2026-04-26 optimized MP4 to fadecandy LEDs, optimized LDR detection
2026-04-28 updates to automates button layouts, bug fixes in fcproxy.cpp
2026-04-29 Automate theme updates
2026-05-01 rate limit slider API calls, minor theme enhancements
2026-05-02 rewrote main automation script in node.js API
2026-05-02 removed obsolete script
2026-05-03 bash script API to native node.js
2026-05-08 Added native WS2812B LED driving to Pi
2026-05-09 added spectrograph effect
2026-05-10 converted all LED effects to C++
2026-05-15 checkpoint #1 (all working LED effects)
2026-05-16 centralized shared code between servers and pi's
2026-05-17 added text scroll LED window to website, misc tweaks
2026-05-18 automate theme tweaks
2026-05-20 code cleanup
2026-05-23 website updates, aptcam improved video quality
2026-06-02 added RS-232 request retry
2026-06-03 added new LED effects
2026-06-11 split up website components, add title-bar room state icon
2026-06-13 added 5-second device status indicator, FIFO queue added to callSerial() in API
2026-06-13 added color selector prompt
2026-06-14 misc optimizations
2026-06-15 switching to module based JS
2026-06-15 switched to module based JS (complete tested)
2026-06-18 switched all power menus to new toggle switches
2026-06-19 website optimizations
2026-06-19 API optimizations
2026-06-20 website and backend optimizations, split main.js into modules
2026-06-20 website and backend optimizations, split main.js into modules #2
2026-06-20 misc website optimizations, made room state icon modular JS
